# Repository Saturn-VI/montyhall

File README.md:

## Basic PCB for the Hack Club Pathfinder YSWS

it's a monty hall game

1. press the start button to start
2. press one of the three buttons
3. an led lights up to reveal a "door" (this one has nothing behind it)
4. press another button and the correct door blinks at the end

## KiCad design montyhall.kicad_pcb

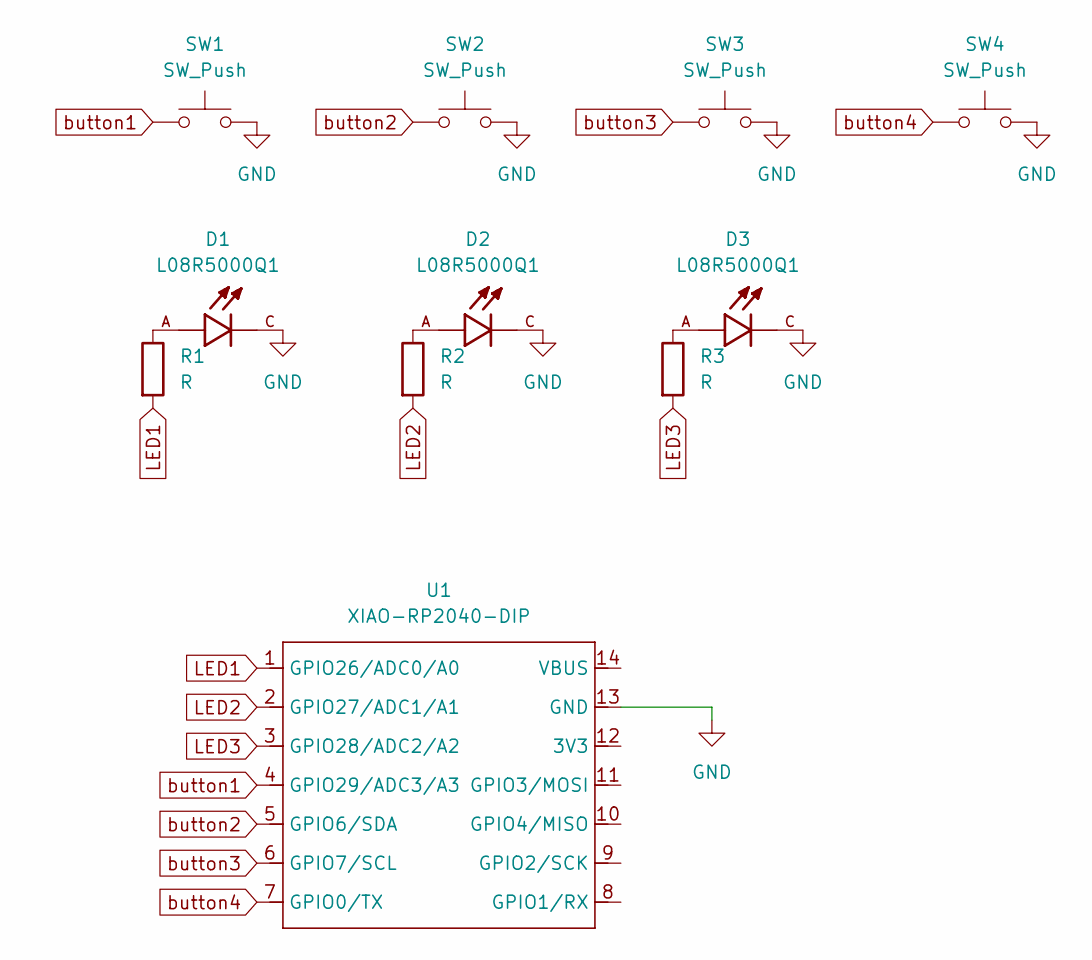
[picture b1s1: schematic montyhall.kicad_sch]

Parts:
D1, D2, D3: L08R5000Q1; LEDRD254W57D500H1070; PARTREV NA
R1, R2, R3: R; R_Axial_DIN0204_L3.6mm_D1.6mm_P5.08mm_Horizontal
SW1, SW2, SW3, SW4: SW_Push; SW_Cherry_MX_1.00u_PCB
U1: XIAO-RP2040-DIP

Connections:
GND: D1.C, D2.C, D3.C, SW1.2, SW2.2, SW3.2, SW4.2, U1.13 (GND)
LED1: R1.2, U1.1 (GPIO26/ADC0/A0)
LED2: R2.2, U1.2 (GPIO27/ADC1/A1)
LED3: R3.2, U1.3 (GPIO28/ADC2/A2)
unnamed: D1.A, R1.1
unnamed: D2.A, R2.1
unnamed: D3.A, R3.1
button1: SW1.1, U1.4 (GPIO29/ADC3/A3)
button2: SW2.1, U1.5 (GPIO6/SDA)
button3: SW3.1, U1.6 (GPIO7/SCL)
button4: SW4.1, U1.7 (GPIO0/TX)

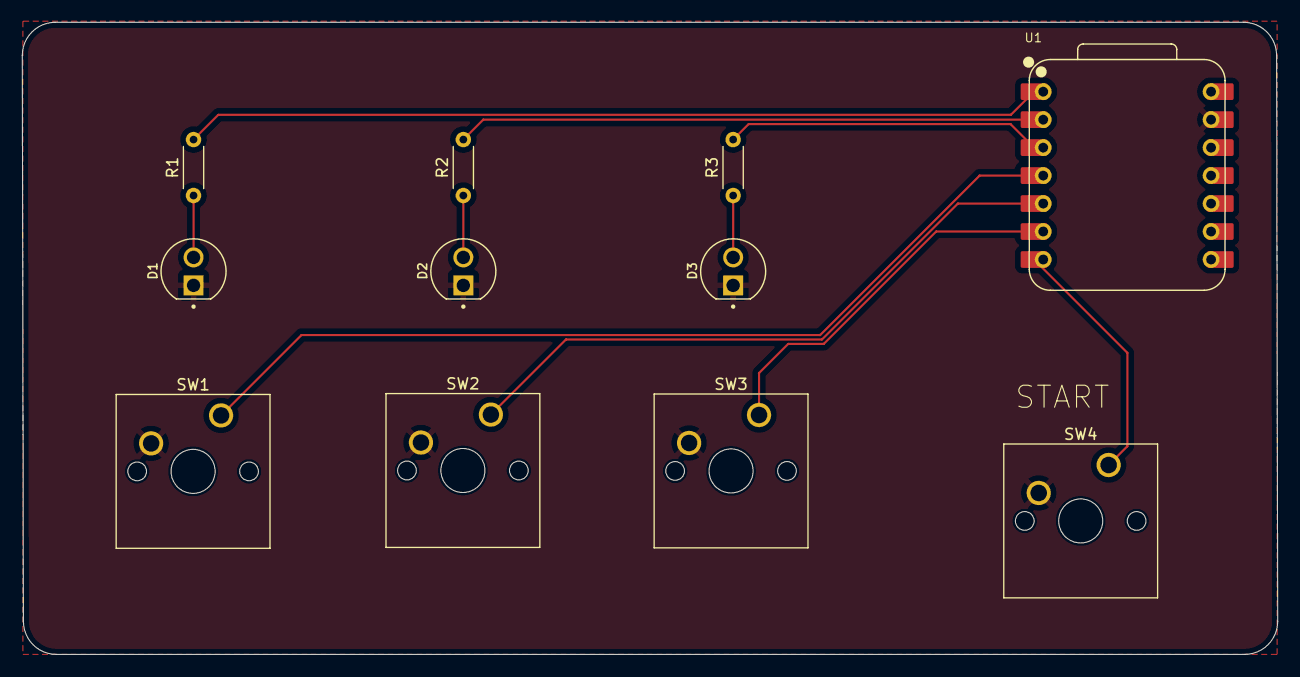
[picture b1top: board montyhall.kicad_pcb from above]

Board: 2 copper layers, 114.0 x 57.4 mm, 11 parts (0 on the bottom side), 11 nets.

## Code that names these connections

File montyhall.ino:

int LED1 = D0;
int LED2 = D1;
int LED3 = D2;

int button1 = D3;
int button2 = D4;
int button3 = D5;
int button4 = D6; // start button

int buttons[] = {button1, button2, button3, button4};

int leds[] = {LED1, LED2, LED3};

int prizeDoor = 0;
int revealedDoor = 0;

bool gameStarted = false;
bool firstDoorPicked = false;

bool wasPressed = false;

void setup() {
  // put your setup code here, to run once:
  pinMode(button1, INPUT_PULLUP);
  pinMode(button2, INPUT_PULLUP);
  pinMode(button3, INPUT_PULLUP);
  pinMode(button4, INPUT_PULLUP);

  pinMode(LED1, OUTPUT);
  pinMode(LED2, OUTPUT);
  pinMode(LED3, OUTPUT);

  randomSeed(analogRead(A0));
}

void loop() {
  // put your main code here, to run repeatedly:
  if (!gameStarted && digitalRead(button4) == LOW) {
    // start
    gameStarted = true;
    wasPressed = true;
    prizeDoor = random(3);
    blinkEverythingTwice();
    return;
  }

  if (!gameStarted) {
    return;
  }

  if (getFirstPressed() == -1 && digitalRead(button4) == HIGH) {
    wasPressed = false;
    return;
  }

  if (wasPressed) {
    // don't want to spam actions
    return;
  }

  wasPressed = true;

  int pressedButton = getFirstPressed();

  if (!firstDoorPicked) {
    firstDoorPicked = true;
    revealedDoor = getRevealDoor(pressedButton, prizeDoor);
    setLed(leds[revealedDoor], HIGH);
  } else {
    if (pressedButton == revealedDoor) {
      return;
    }
    // no matter what just blink the correct door
    blinkLed(leds[prizeDoor]);
    gameStarted = false;
  }
}

// assumes at least one button is pressed
int getFirstPressed() {
  for (int i = 0; i < 3; i++) {
    if (digitalRead(buttons[i]) == LOW) {
      return i;
    }
  }
  return -1;
}

void blinkEverythingTwice() {
  for (int i = 0; i < 2; i++) {
    setAllLeds(HIGH);
    delay(500);
    setAllLeds(LOW);
    delay(500);
  }
}

void blinkLed(int ledid) {
    setAllLeds(LOW);
    setLed(ledid, HIGH);
    delay(500);
    setLed(ledid, LOW);
    delay(500);
}

void setAllLeds(int state) {
  for (int i = 0; i < sizeof(leds)/sizeof(leds[0]); i++) {
    digitalWrite(leds[i], state);
  }
}

void setLed(int id, int state) {
  digitalWrite(id, state);
}

int getRevealDoor(int selectedDoor, int prizeDoor) {
  int revealDoor;
  if (selectedDoor == prizeDoor) {
    revealDoor = random(2);
    if (revealDoor >= selectedDoor) {
      revealDoor++;
    }
  } else {
    revealDoor = 0;
    while (revealDoor == selectedDoor || revealDoor == prizeDoor) {
      revealDoor++;
    }
  }
  return revealDoor;
}
